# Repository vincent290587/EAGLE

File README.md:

# EAGLE

Here is a list of Eagle library files, useful if you want to use SD cards, Dynastream ANT+ chips, Freescale MCUs or a STC3100 to monitor current consumption and battery discharge level.

- N548: Dynastream N548/N550/N5150 M8 footprint module
- ANTAP28: Dynastream N548/N550/N5150 M4 footprint module
- D52Q: Dynastream new D52Q module, using nRF52832 from Nordic
- nRF52840: Nordic bluetooth 5 new chip
- MK20DN512: Footprint for Freescale 100 pins MKxx family (MK20, MK64.......)

- FlashMem: Footprint for SPI flash chips like Microchip SST25VF & SS26VF

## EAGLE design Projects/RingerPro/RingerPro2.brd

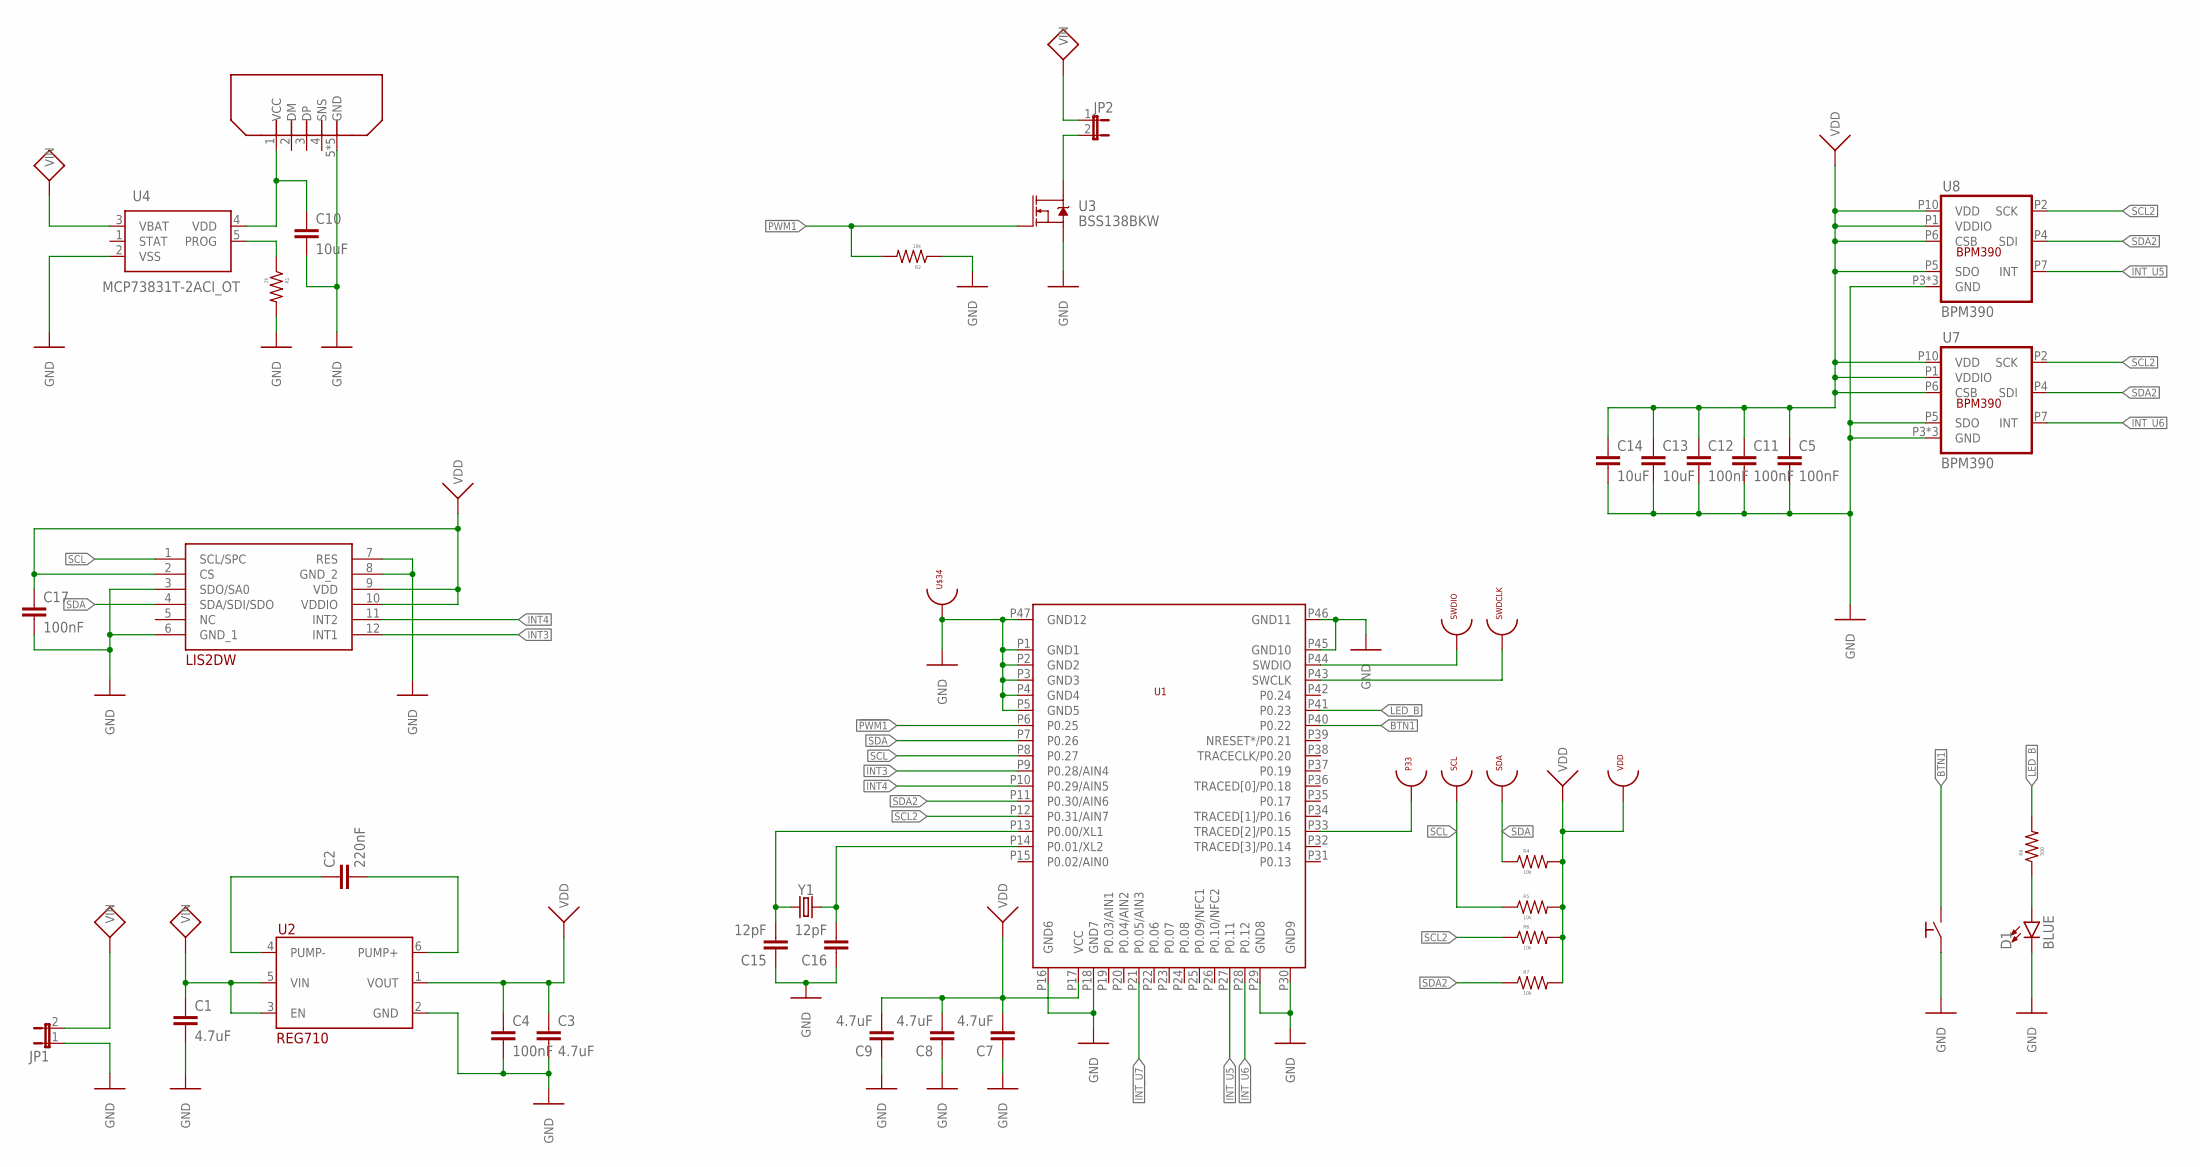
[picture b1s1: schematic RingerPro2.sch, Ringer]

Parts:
C1, C3, C7, C8, C9: 4.7uF; C0603
C2: 220nF; C0603
C4, C5, C11, C12, C17: 100nF; C0603
C10, C13, C14: 10uF; C0603
C15, C16: 12pF; C0603
D1: BLUE; LED-0603
IC1: LIS2DW12TR; LGA-12
JP1, JP2: JP1E; JP1
P33: TESTPOINT_22
R1: 2k; R0603
R2, R4, R5, R6, R7: 10k; R0603
R9: 500; R0603
SCL: TESTPOINT_22
SDA: TESTPOINT_22
SPST1: PTS526SK08; PTS526SKG15SMTR2LFS
SWDCLK: TESTPOINT_22
SWDIO: TESTPOINT_22
U1: BMD-300
U2: REG710; SOT457
U3: BSS138BKW; SOT65P210X110-3N
U4: MCP73831T-2ACI_OT; SOT95P270X145-5N
U7, U8: BPM390
U$23: ZX80B5P
U$34: TESTPOINT_22
VDD: TESTPOINT_22
Y1: CRYSTALSMD-3.2X1.5; CRYSTAL-SMD-3.2X1.5MM

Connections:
!PWM1: R2.2, U1.P6 (P0.25), U3.1 (G)
BTN1: SPST1.3, SPST1.4, U1.P40 (P0.22)
GND: C1.2, C3.2, C4.2, C5.2, C7.1, C8.1, C9.1, C10.2, C11.2, C12.2, C13.2, C14.2, C15.1, C16.1, C17.2, D1.C, IC1.3 (SDO/SA0), IC1.6 (GND_1), IC1.7 (RES), IC1.8 (GND_2), JP1.1, R1.2, R2.1, SPST1.1, SPST1.2, U1.P1 (GND1), U1.P2 (GND2), U1.P3 (GND3), U1.P4 (GND4), U1.P5 (GND5), U1.P16 (GND6), U1.P18 (GND7), U1.P29 (GND8), U1.P30 (GND9), U1.P45 (GND10), U1.P46 (GND11), U1.P47 (GND12), U2.2 (GND), U3.2 (S), U4.2 (VSS), U7.P3 (GND), U7.P5 (SDO), U7.P8 (GND), U7.P9 (GND), U8.P3 (GND), U8.P8 (GND), U8.P9 (GND), U$23.5 (GND), U$23.GND1 (GND), U$23.GND2 (GND), U$23.GND3 (GND), U$23.GND4 (GND), U$34.P$1
INT3: IC1.12 (INT1), U1.P9 (P0.28/AIN4)
INT4: IC1.11 (INT2), U1.P10 (P0.29/AIN5)
INT_U5: U1.P27 (P0.11), U8.P7 (INT)
INT_U6: U1.P28 (P0.12), U7.P7 (INT)
INT_U7: U1.P21 (P0.05/AIN3)
LED_B: R9.2, U1.P41 (P0.23)
unnamed: C2.1, U2.4 (PUMP-)
unnamed: C2.2, U2.6 (PUMP+)
unnamed: C10.1, U4.4 (VDD), U$23.1 (VCC)
unnamed: C15.2, U1.P13 (P0.00/XL1), Y1.P$1 (1)
unnamed: R1.1, U4.5 (PROG)
unnamed: JP2.2, U3.3 (D)
unnamed: C16.2, U1.P14 (P0.01/XL2), Y1.P$2 (2)
unnamed: P33.P$1, U1.P33 (TRACED[2]/P0.15)
unnamed: D1.A, R9.1
SCL: IC1.1 (SCL/SPC), R5.1, SCL.P$1, U1.P8 (P0.27)
SCL2: R6.1, U1.P12 (P0.31/AIN7), U7.P2 (SCK), U8.P2 (SCK)
SDA: IC1.4 (SDA/SDI/SDO), R4.1, SDA.P$1, U1.P7 (P0.26)
SDA2: R7.1, U1.P11 (P0.30/AIN6), U7.P4 (SDI), U8.P4 (SDI)
SWCLK: SWDCLK.P$1, U1.P43 (SWCLK)
SWDIO: SWDIO.P$1, U1.P44 (SWDIO)
VDD: C3.1, C4.1, C5.1, C7.2, C8.2, C9.2, C11.1, C12.1, C13.1, C14.1, C17.1, IC1.2 (CS), IC1.9 (VDD), IC1.10 (VDDIO), R4.2, R5.2, R6.2, R7.2, U1.P17 (VCC), U2.1 (VOUT), U7.P1 (VDDIO), U7.P6 (CSB), U7.P10 (VDD), U8.P1 (VDDIO), U8.P5 (SDO), U8.P6 (CSB), U8.P10 (VDD), VDD.P$1
VIN: C1.1, JP1.2, JP2.1, U2.3 (EN), U2.5 (VIN), U4.3 (VBAT)

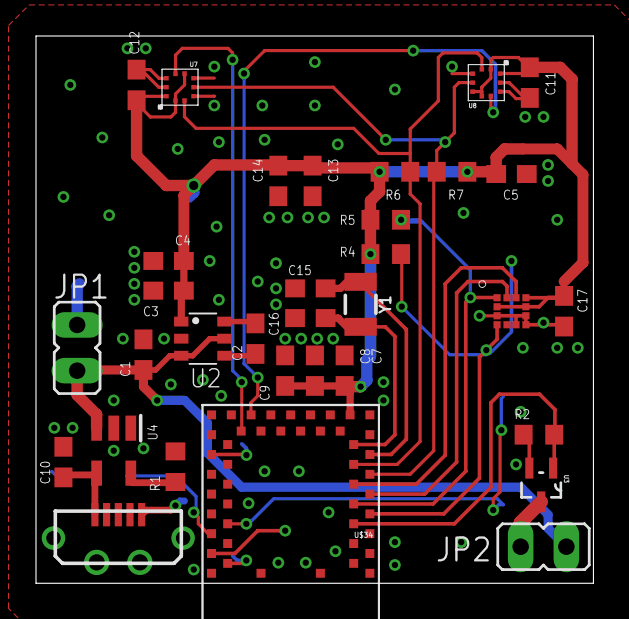
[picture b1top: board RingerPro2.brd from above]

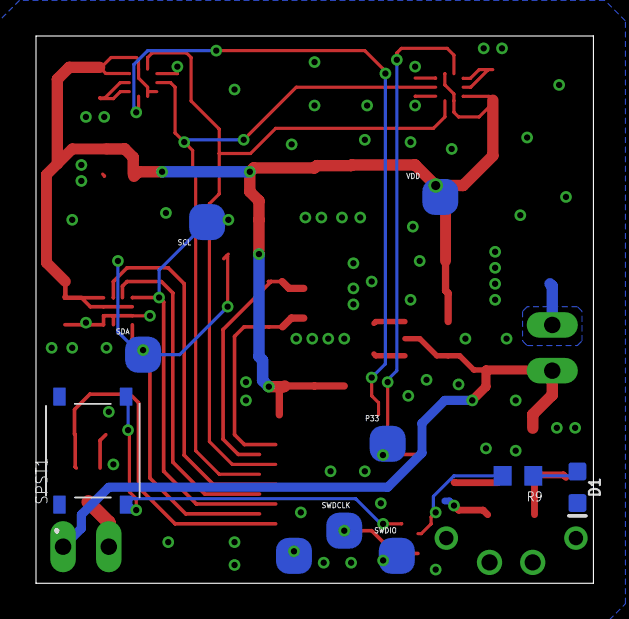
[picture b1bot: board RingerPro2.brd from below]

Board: 2 copper layers, 31.0 x 30.4 mm, 43 parts (10 on the bottom side), 25 nets.

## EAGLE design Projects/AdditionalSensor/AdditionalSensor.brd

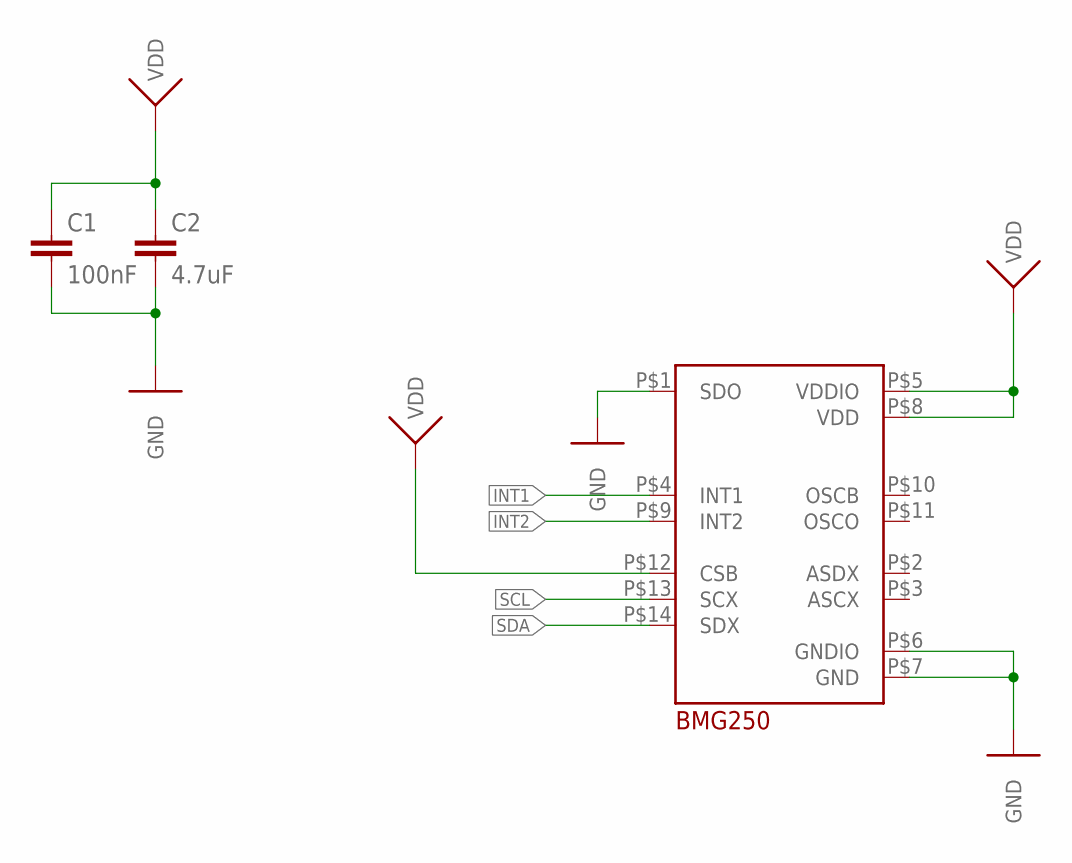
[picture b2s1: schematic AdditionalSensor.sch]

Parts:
C1: 100nF; C0603
C2: 4.7uF; C0603
U1: BMG250; LGA14

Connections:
GND: C1.2, C2.2, U1.P$1 (SDO), U1.P$6 (GNDIO), U1.P$7 (GND)
INT1: U1.P$4 (INT1)
INT2: U1.P$9 (INT2)
SCL: U1.P$13 (SCX)
SDA: U1.P$14 (SDX)
VDD: C1.1, C2.1, U1.P$5 (VDDIO), U1.P$8 (VDD), U1.P$12 (CSB)

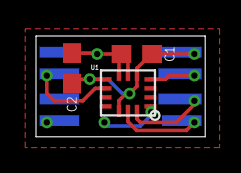
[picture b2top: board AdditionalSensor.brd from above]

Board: 2 copper layers, 9.4 x 5.6 mm, 3 parts (0 on the bottom side), 2 nets.

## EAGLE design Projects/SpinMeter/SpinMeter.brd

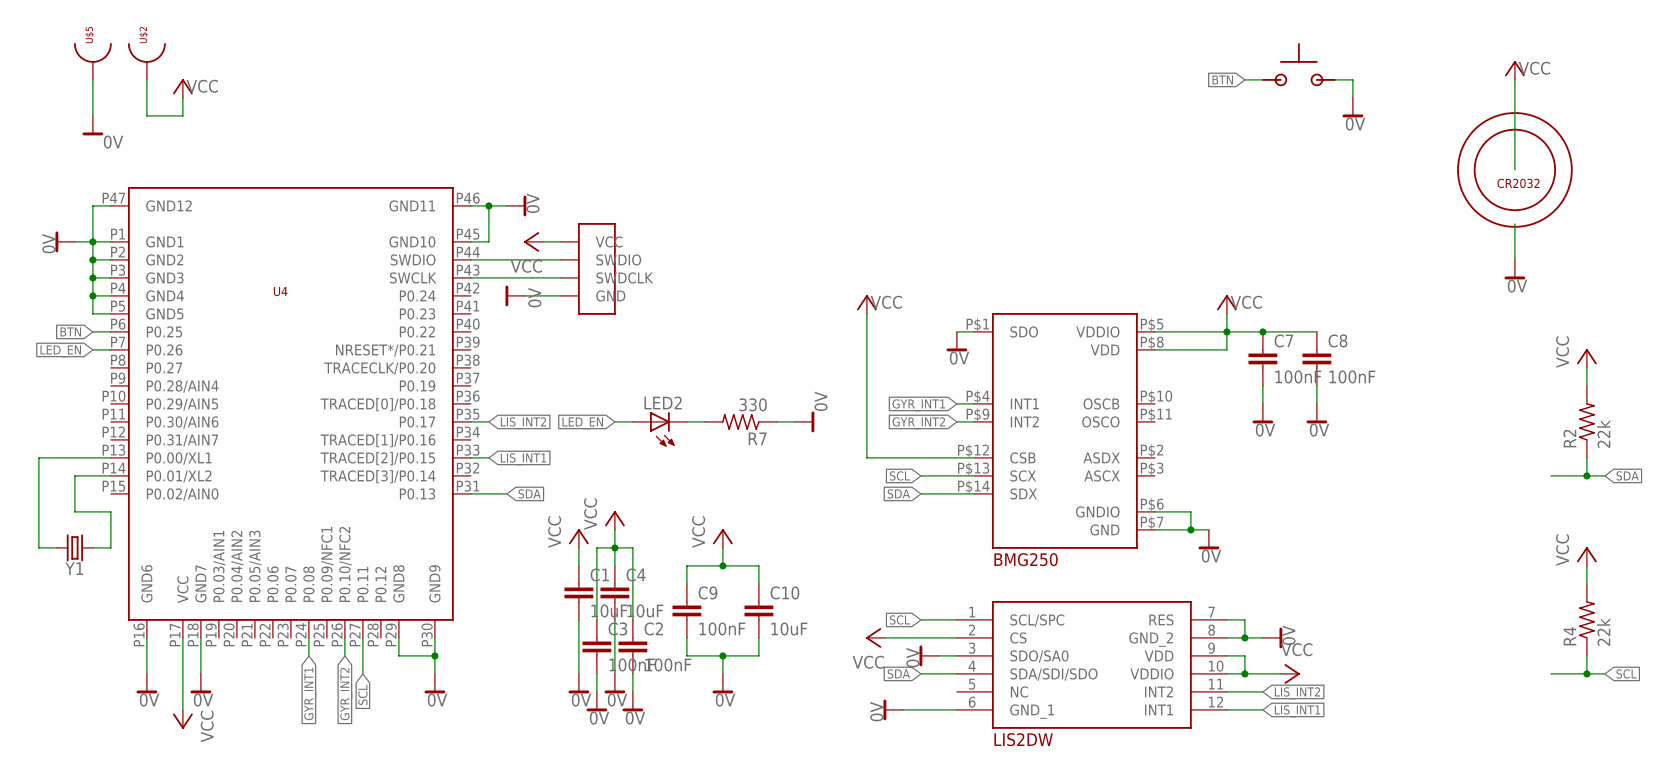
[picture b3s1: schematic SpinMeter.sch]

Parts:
C1, C4, C10: 10uF; C0603
C2, C3, C7, C8, C9: 100nF; C0603
IC1: LIS2DW12TR; LGA-12
LED2: LEDCHIP-LED0603; CHIP-LED0603
R2, R4: 22k; R0603
R7: 330; R0603
U1: BMG250; LGA14
U3: BAT-HLD-001-THM; BATHLD001THM
U4: BMD-300
U$1: PROG_SMD
U$2, U$5: TESTPOINT_22
U$10: SKRMAAE010
Y1: CRYSTALSMD-3.2X1.5; CRYSTAL-SMD-3.2X1.5MM

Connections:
0V: C1.2, C2.2, C3.2, C4.2, C7.2, C8.2, C9.2, C10.2, IC1.3 (SDO/SA0), IC1.6 (GND_1), IC1.7 (RES), IC1.8 (GND_2), R7.1, U1.P$1 (SDO), U1.P$6 (GNDIO), U1.P$7 (GND), U3.5 (-), U4.P1 (GND1), U4.P2 (GND2), U4.P3 (GND3), U4.P4 (GND4), U4.P5 (GND5), U4.P16 (GND6), U4.P18 (GND7), U4.P29 (GND8), U4.P30 (GND9), U4.P45 (GND10), U4.P46 (GND11), U4.P47 (GND12), U$1.GND, U$5.P$1, U$10.P$2, U$10.P$4
BTN: U4.P6 (P0.25), U$10.P$1, U$10.P$3
GYR_INT1: U1.P$4 (INT1), U4.P24 (P0.08)
GYR_INT2: U1.P$9 (INT2), U4.P26 (P0.10/NFC2)
LED_EN: LED2.A, U4.P7 (P0.26)
LIS_INT1: IC1.12 (INT1), U4.P33 (TRACED[2]/P0.15)
LIS_INT2: IC1.11 (INT2), U4.P35 (P0.17)
unnamed: U4.P44 (SWDIO), U$1.PIN2 (SWDIO)
unnamed: U4.P43 (SWCLK), U$1.PIN1 (SWDCLK)
unnamed: LED2.C, R7.2
unnamed: U4.P13 (P0.00/XL1), Y1.P$2 (2)
unnamed: U4.P14 (P0.01/XL2), Y1.P$1 (1)
SCL: IC1.1 (SCL/SPC), R4.1, U1.P$13 (SCX), U4.P27 (P0.11)
SDA: IC1.4 (SDA/SDI/SDO), R2.1, U1.P$14 (SDX), U4.P31 (P0.13)
VCC: C1.1, C2.1, C3.1, C4.1, C7.1, C8.1, C9.1, C10.1, IC1.2 (CS), IC1.9 (VDD), IC1.10 (VDDIO), R2.2, R4.2, U1.P$5 (VDDIO), U1.P$8 (VDD), U1.P$12 (CSB), U3.1 (+), U3.2 (+), U3.3 (+), U3.4 (+), U4.P17 (VCC), U$1.VCC, U$2.P$1

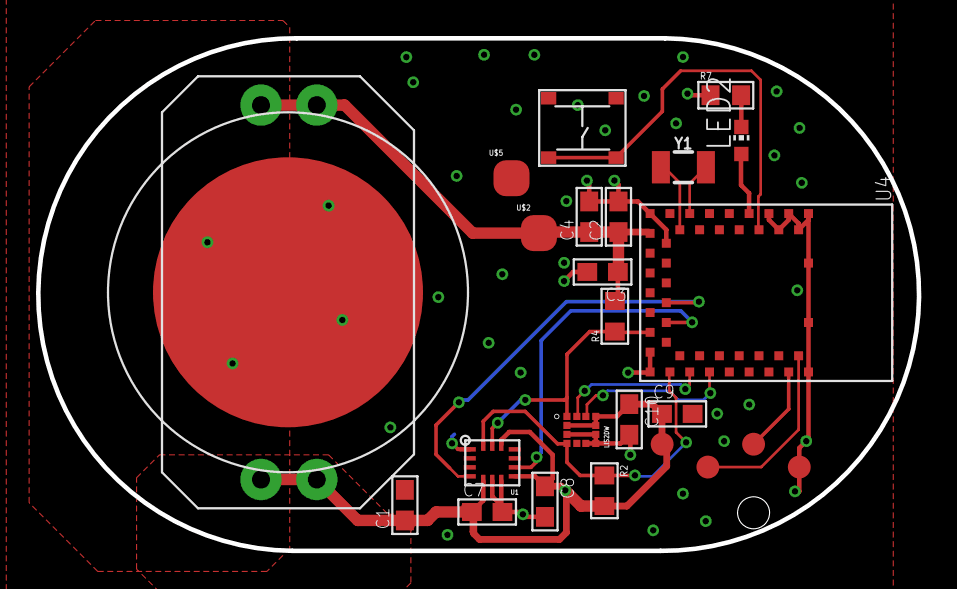
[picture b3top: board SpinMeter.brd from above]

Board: 2 copper layers, 48.9 x 28.5 mm, 21 parts (0 on the bottom side), 15 nets.

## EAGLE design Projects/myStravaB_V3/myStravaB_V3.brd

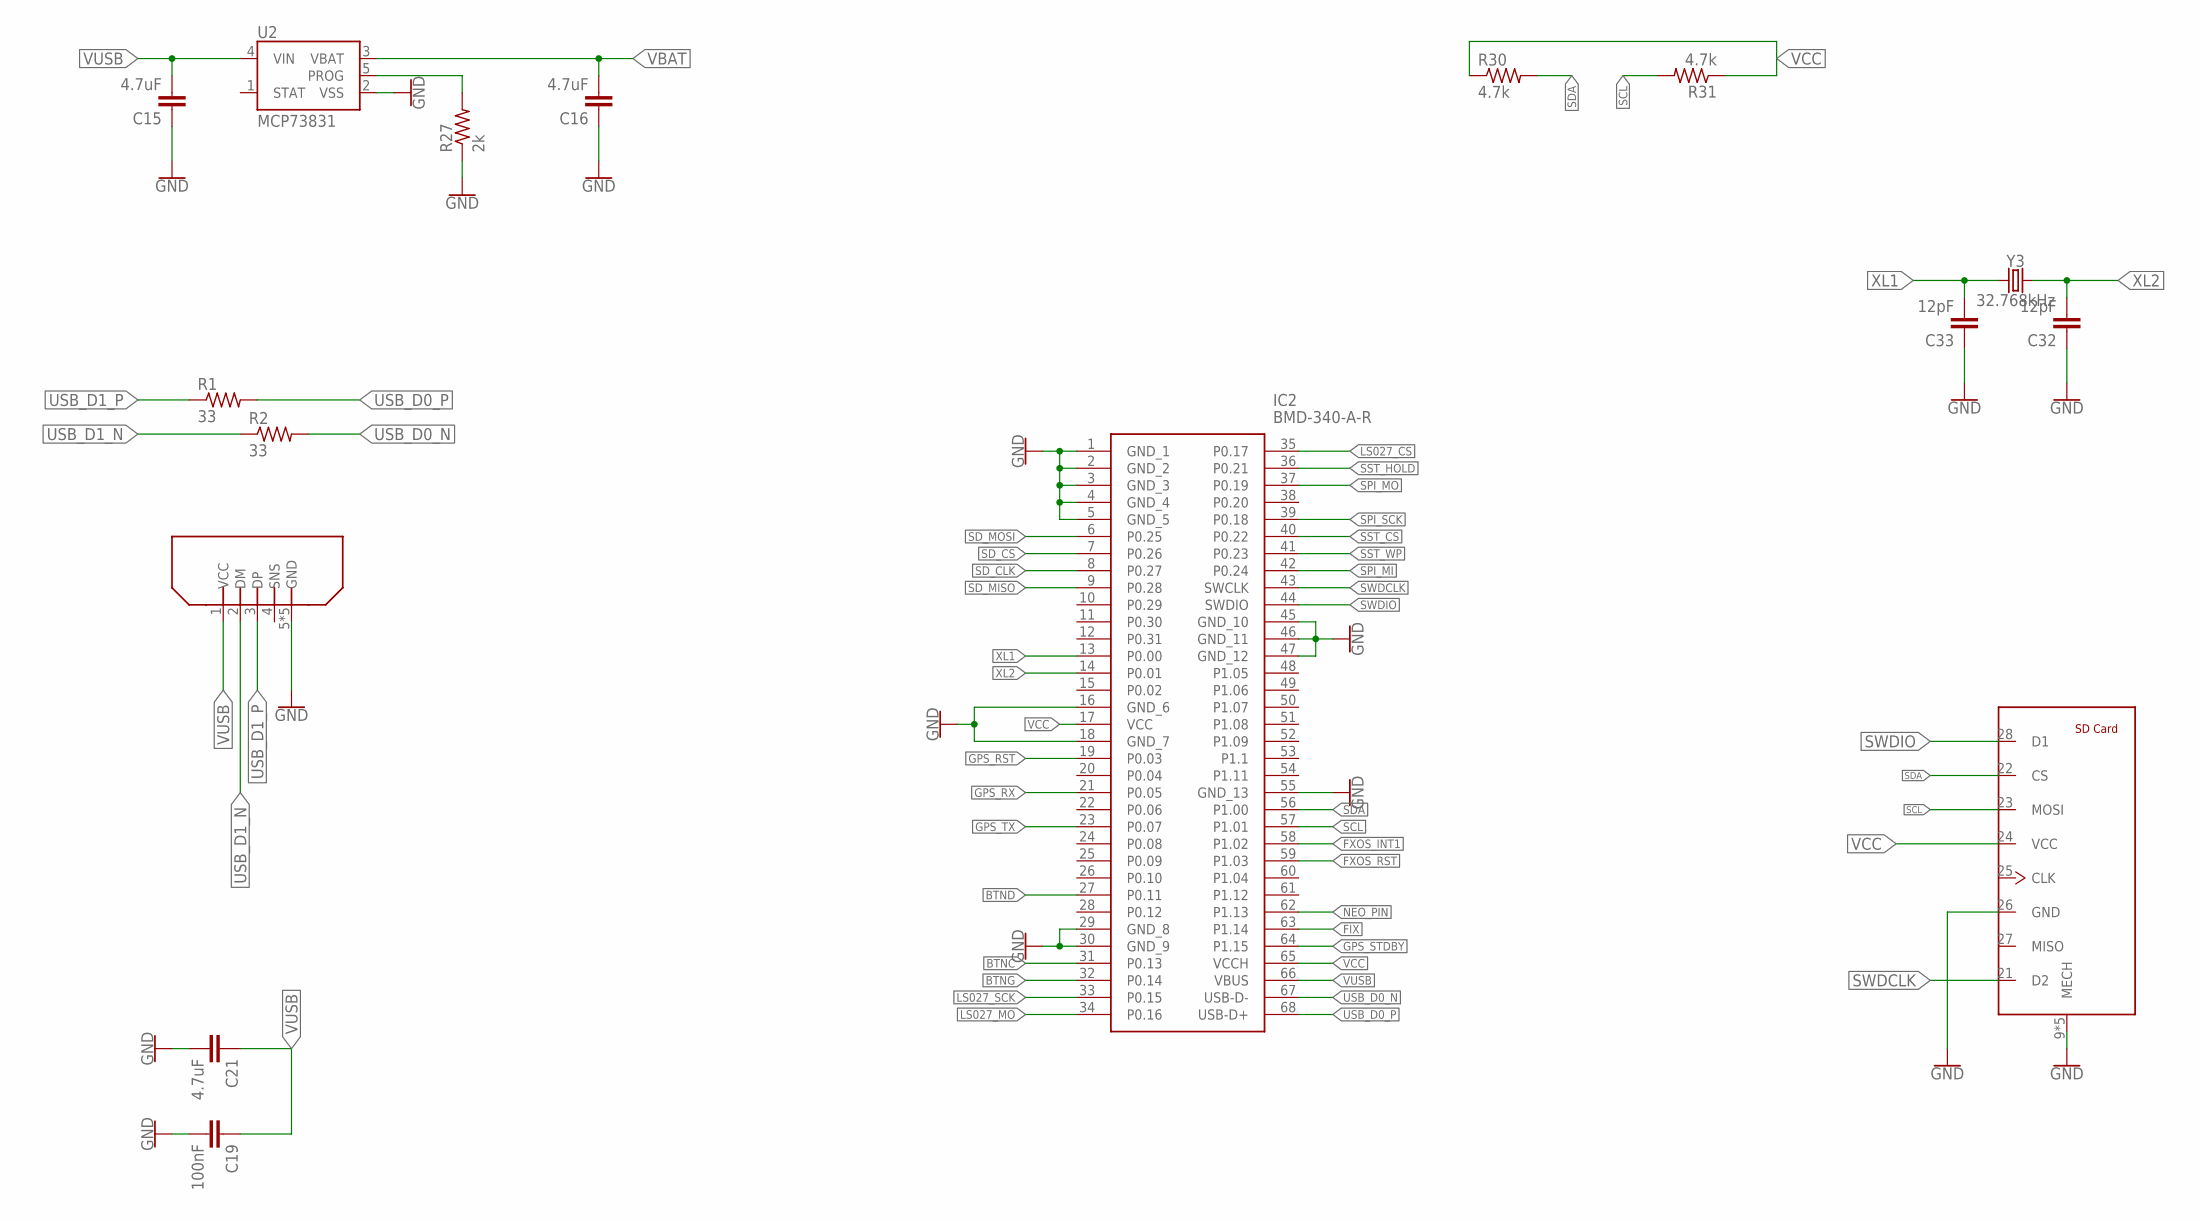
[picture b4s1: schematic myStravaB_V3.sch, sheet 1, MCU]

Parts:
C15, C16, C21: 4.7uF; C0805
C19: 100nF; C0603
C32, C33: 12pF; C0603
IC2: BMD-340-A-R; BMD340AR
J1: 47571-0001
R1, R2: 33; R0603
R27: 2k; R0603
R30, R31: 4.7k; R0603
U2: MCP73831; SOT23-5
U$3: ZX80B5P
Y3: 32.768kHz; CRYSTAL-SMD-3.2X1.5MM

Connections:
BTNC: IC2.31 (P0.13); also elsewhere on the board
BTND: IC2.27 (P0.11); also elsewhere on the board
BTNG: IC2.32 (P0.14); also elsewhere on the board
FIX: IC2.63 (P1.14); also elsewhere on the board
FXOS_INT1: IC2.58 (P1.02); also elsewhere on the board
FXOS_RST: IC2.59 (P1.03); also elsewhere on the board
GND: C15.1, C16.1, C19.2, C21.2, C32.1, C33.1, IC2.1 (GND_1), IC2.2 (GND_2), IC2.3 (GND_3), IC2.4 (GND_4), IC2.5 (GND_5), IC2.16 (GND_6), IC2.18 (GND_7), IC2.29 (GND_8), IC2.30 (GND_9), IC2.45 (GND_10), IC2.46 (GND_11), IC2.47 (GND_12), IC2.55 (GND_13), J1.9 (MECH), J1.10 (MECH), J1.11 (MECH), J1.12 (MECH), J1.13 (MECH), J1.26 (GND), R27.1, U2.2 (VSS), U$3.5 (GND), U$3.GND1 (GND), U$3.GND2 (GND), U$3.GND3 (GND), U$3.GND4 (GND); also elsewhere on the board
GPS_RST: IC2.19 (P0.03); also elsewhere on the board
GPS_RX: IC2.21 (P0.05); also elsewhere on the board
GPS_STDBY: IC2.64 (P1.15); also elsewhere on the board
GPS_TX: IC2.23 (P0.07); also elsewhere on the board
LS027_CS: IC2.35 (P0.17); also elsewhere on the board
LS027_MO: IC2.34 (P0.16); also elsewhere on the board
LS027_SCK: IC2.33 (P0.15); also elsewhere on the board
unnamed: R27.2, U2.5 (PROG)
NEO_PIN: IC2.62 (P1.13); also elsewhere on the board
SCL: IC2.57 (P1.01), J1.23 (MOSI), R31.2; also elsewhere on the board
SDA: IC2.56 (P1.00), J1.22 (CS), R30.2; also elsewhere on the board
SD_CLK: IC2.8 (P0.27); also elsewhere on the board
SD_CS: IC2.7 (P0.26); also elsewhere on the board
SD_MISO: IC2.9 (P0.28); also elsewhere on the board
SD_MOSI: IC2.6 (P0.25); also elsewhere on the board
SPI_MI: IC2.42 (P0.24); also elsewhere on the board
SPI_MO: IC2.37 (P0.19); also elsewhere on the board
SPI_SCK: IC2.39 (P0.18); also elsewhere on the board
SST_CS: IC2.40 (P0.22); also elsewhere on the board
SST_HOLD: IC2.36 (P0.21); also elsewhere on the board
SST_WP: IC2.41 (P0.23); also elsewhere on the board
SWDCLK: IC2.43 (SWCLK), J1.21 (D2)
SWDIO: IC2.44 (SWDIO), J1.28 (D1)
USB_D0_N: IC2.67 (USB-D-), R2.2
USB_D0_P: IC2.68 (USB-D+), R1.2
USB_D1_N: R2.1, U$3.2 (DM)
USB_D1_P: R1.1, U$3.3 (DP)
VBAT: C16.2, U2.3 (VBAT); also elsewhere on the board
VCC: IC2.17 (VCC), IC2.65 (VCCH), J1.24 (VCC), R30.1, R31.1; also elsewhere on the board
VUSB: C15.2, C19.1, C21.1, IC2.66 (VBUS), U2.4 (VIN), U$3.1 (VCC); also elsewhere on the board
XL1: C33.2, IC2.13 (P0.00), Y3.P$1 (1)
XL2: C32.2, IC2.14 (P0.01), Y3.P$2 (2)

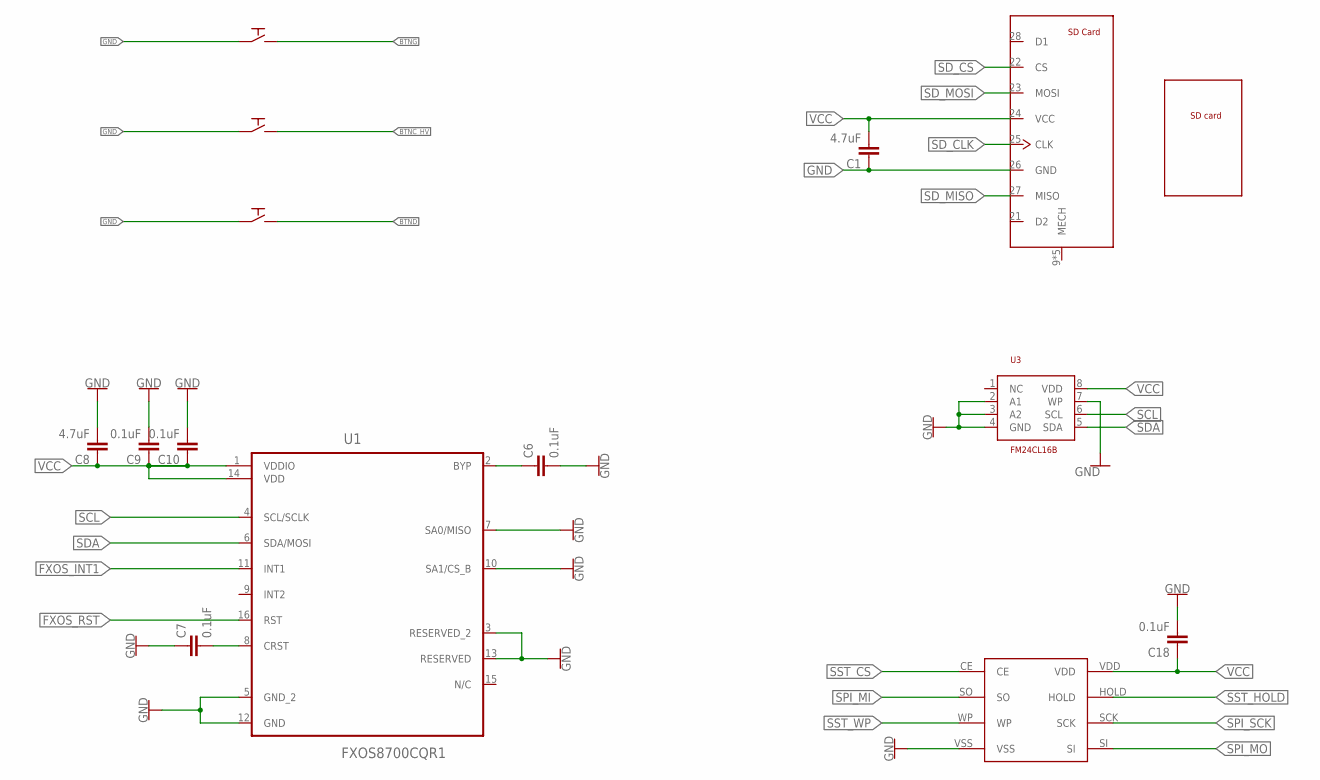
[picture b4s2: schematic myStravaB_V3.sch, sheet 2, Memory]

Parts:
B1: MICRO-SD_FOOTPRINT; MICRO-SD-FOOTPRINT
C1, C8: 4.7uF; 0603
C6, C7, C9, C10, C18: 0.1uF; 0603
SD: 47571-0001
SPST1, SPST2, SPST3: PTS526SK08; PTS526SKG15SMTR2LFS
U1: FXOS8700CQR1; QFN50P300X300X120-16N
U3: FM24CL16B; SOIC127P600X175-8N
U$2: FLASH; SOIC8

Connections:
BTNC_HV: SPST2.3, SPST2.4; also elsewhere on the board
BTND: SPST3.3, SPST3.4; also elsewhere on the board
BTNG: SPST1.3, SPST1.4; also elsewhere on the board
BYP: C6.1, U1.2 (BYP)
CRST: C7.2, U1.8 (CRST)
FXOS_INT1: U1.11 (INT1); also elsewhere on the board
FXOS_RST: U1.16 (RST); also elsewhere on the board
GND: C1.1, C6.2, C7.1, C8.2, C9.2, C10.2, C18.2, SD.26 (GND), SPST1.1, SPST1.2, SPST2.1, SPST2.2, SPST3.1, SPST3.2, U1.3 (RESERVED_2), U1.5 (GND_2), U1.7 (SA0/MISO), U1.10 (SA1/CS_B), U1.12 (GND), U1.13 (RESERVED), U3.2 (A1), U3.3 (A2), U3.4 (GND), U3.7 (WP), U$2.VSS; also elsewhere on the board
SCL: U1.4 (SCL/SCLK), U3.6 (SCL); also elsewhere on the board
SDA: U1.6 (SDA/MOSI), U3.5 (SDA); also elsewhere on the board
SD_CLK: SD.25 (CLK); also elsewhere on the board
SD_CS: SD.22 (CS); also elsewhere on the board
SD_MISO: SD.27 (MISO); also elsewhere on the board
SD_MOSI: SD.23 (MOSI); also elsewhere on the board
SPI_MI: U$2.SO; also elsewhere on the board
SPI_MO: U$2.SI; also elsewhere on the board
SPI_SCK: U$2.SCK; also elsewhere on the board
SST_CS: U$2.CE; also elsewhere on the board
SST_HOLD: U$2.HOLD; also elsewhere on the board
SST_WP: U$2.WP; also elsewhere on the board
VCC: C1.2, C8.1, C9.1, C10.1, C18.1, SD.24 (VCC), U1.1 (VDDIO), U1.14 (VDD), U3.8 (VDD), U$2.VDD; also elsewhere on the board

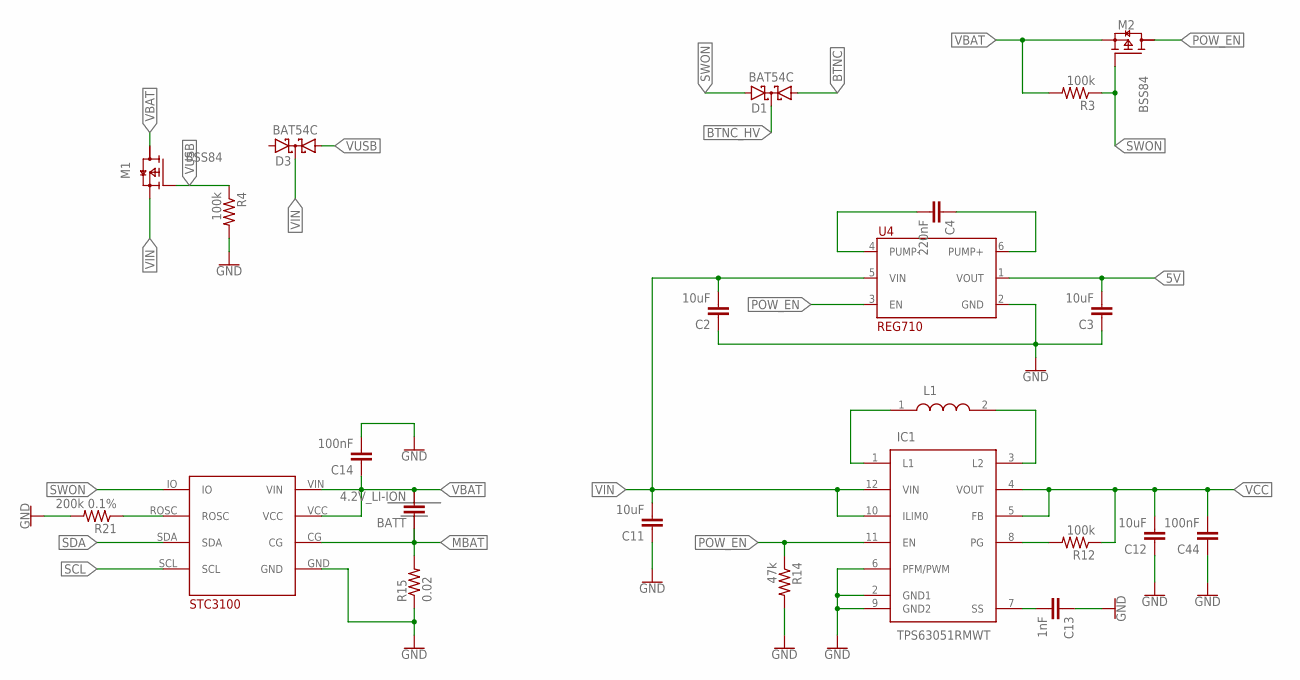
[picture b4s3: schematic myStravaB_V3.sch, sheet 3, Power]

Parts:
BATT: 4.2V_LI-ION; C1210
C2, C3, C11: 10uF; C0805
C4: 220nF; C0805
C12: 10uF; C0603
C13: 1nF; C0603
C14, C44: 100nF; C0603
D1, D3: BAT54C; SOT23
IC1: TPS63051RMWT; QFN50P250X250X100-12N
L1: 1269AS-H-1R5M=P2; INDC2520X110N
M1, M2: BSS84; SOT65P210X110-3N
R3, R4, R12: 100k; R0603
R14: 47k; R0603
R15: 0.02; R0603
R21: 200k 0.1%; R0603
U4: REG710; SOT457
U$6: STC3100

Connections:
5V: C3.2, U4.1 (VOUT); also elsewhere on the board
BTNC: D1.1 (A1); also elsewhere on the board
BTNC_HV: D1.3 (CC); also elsewhere on the board
GND: C2.1, C3.1, C11.1, C12.1, C13.1, C14.2, C44.1, IC1.2 (GND1), IC1.6 (PFM/PWM), IC1.9 (GND2), R4.2, R14.2, R15.1, R21.2, U4.2 (GND), U$6.GND; also elsewhere on the board
L1: IC1.1 (L1), L1.1
L2: IC1.3 (L2), L1.2
MBAT: BATT.1, R15.2, U$6.CG
unnamed: C4.1, U4.6 (PUMP+)
unnamed: C4.2, U4.4 (PUMP-)
PG: IC1.8 (PG), R12.2
POW_EN: IC1.11 (EN), M2.3 (D), R14.1, U4.3 (EN)
ROSC: R21.1, U$6.ROSC
SCL: U$6.SCL; also elsewhere on the board
SDA: U$6.SDA; also elsewhere on the board
SS: C13.2, IC1.7 (SS)
SWON: D1.2 (A2), M2.1 (G), R3.1, U$6.IO
VBAT: BATT.2, C14.1, M1.3 (D), M2.2 (S), R3.2, U$6.VCC, U$6.VIN; also elsewhere on the board
VCC: C12.2, C44.2, IC1.4 (VOUT), IC1.5 (FB), R12.1; also elsewhere on the board
VIN: C2.2, C11.2, D3.3 (CC), IC1.10 (ILIM0), IC1.12 (VIN), M1.2 (S), U4.5 (VIN)
VUSB: D3.1 (A1), M1.1 (G), R4.1; also elsewhere on the board

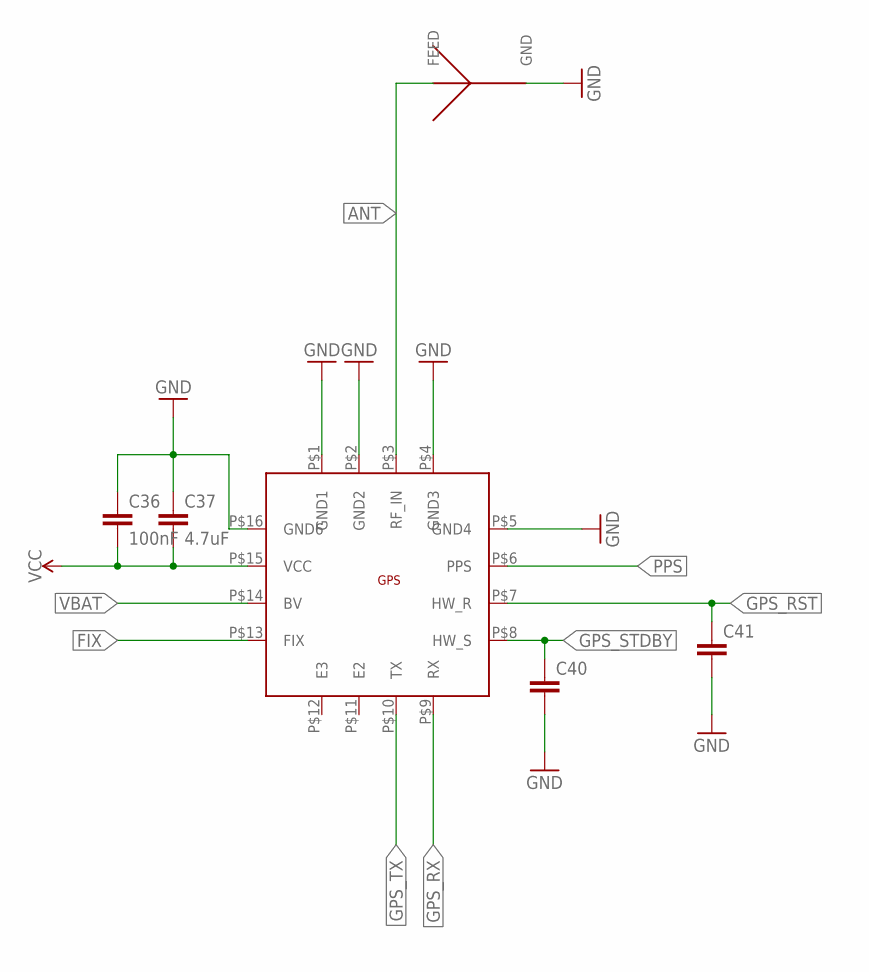
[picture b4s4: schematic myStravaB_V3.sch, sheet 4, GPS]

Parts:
C36: 100nF; C0603
C37: 4.7uF; C0603
C40, C41: C-EUC0603; C0603
U$4: SR4G008
U$5: M10578-A3; M10578

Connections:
ANT: U$4.P$2 (FEED), U$5.P$3 (RF_IN)
FIX: U$5.P$13 (FIX); also elsewhere on the board
GND: C36.1, C37.1, C40.2, C41.2, U$4.P$3 (GND), U$4.P$4 (GND), U$4.P$6 (GND), U$5.P$1 (GND1), U$5.P$2 (GND2), U$5.P$4 (GND3), U$5.P$5 (GND4), U$5.P$16 (GND6); also elsewhere on the board
GPS_RST: C41.1, U$5.P$7 (HW_R); also elsewhere on the board
GPS_RX: U$5.P$9 (RX); also elsewhere on the board
GPS_STDBY: C40.1, U$5.P$8 (HW_S); also elsewhere on the board
GPS_TX: U$5.P$10 (TX); also elsewhere on the board
PPS: U$5.P$6 (PPS)
VBAT: U$5.P$14 (BV); also elsewhere on the board
VCC: C36.2, C37.2, U$5.P$15 (VCC); also elsewhere on the board

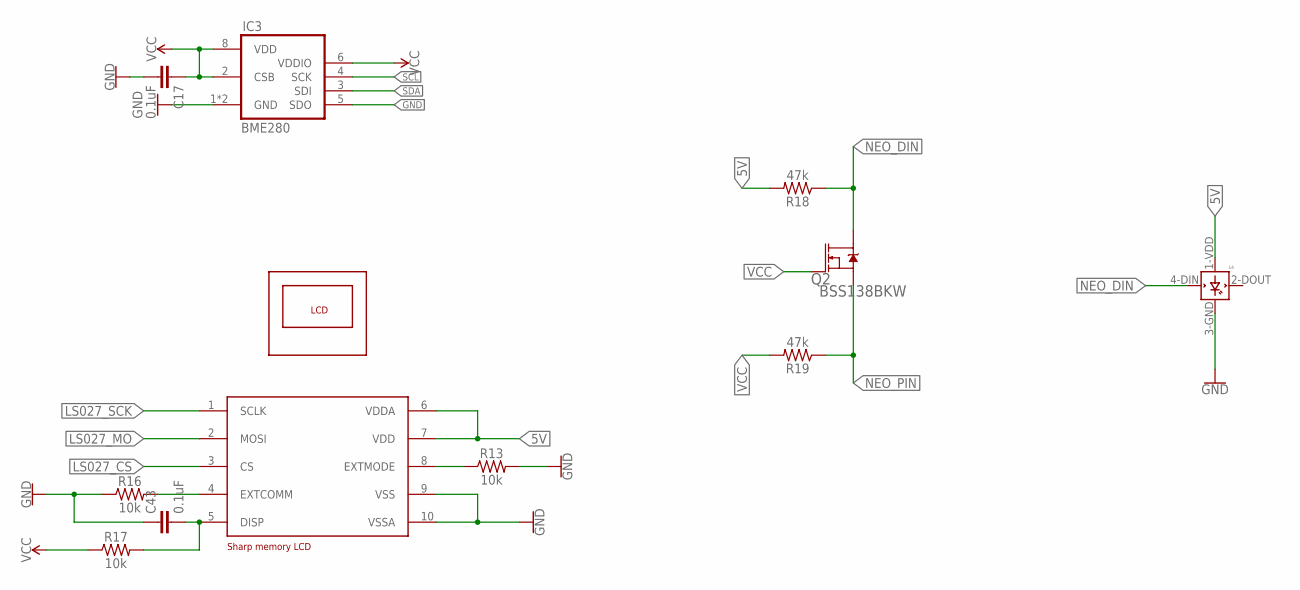
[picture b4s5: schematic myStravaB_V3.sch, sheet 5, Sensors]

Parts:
C17, C43: 0.1uF; 0603
IC3: BME280
L4: WS2812B
Q2: BSS138BKW; SOT65P210X110-3N
R13, R16, R17: 10k; 0603
R18, R19: 47k; 0603
U$15: SHARP27_FOOTPRINT; LCD27
U$16: SHARP27

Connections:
5V: L4.1-VDD (VDD), R18.2, U$16.6 (VDDA), U$16.7 (VDD); also elsewhere on the board
DISP1: C43.2, R17.2, U$16.5 (DISP)
EXTCOMM1: R16.2, U$16.4 (EXTCOMM)
EXTMODE1: R13.1, U$16.8 (EXTMODE)
GND: C17.2, C43.1, IC3.1 (GND), IC3.5 (SDO), IC3.7 (GND), L4.3-GND (GND), R13.2, R16.1, U$16.9 (VSS), U$16.10 (VSSA); also elsewhere on the board
LS027_CS: U$16.3 (CS); also elsewhere on the board
LS027_MO: U$16.2 (MOSI); also elsewhere on the board
LS027_SCK: U$16.1 (SCLK); also elsewhere on the board
NEO_DIN: L4.4-DIN (DIN), Q2.3 (D), R18.1
NEO_PIN: Q2.2 (S), R19.1; also elsewhere on the board
SCL: IC3.4 (SCK); also elsewhere on the board
SDA: IC3.3 (SDI); also elsewhere on the board
VCC: C17.1, IC3.2 (CSB), IC3.6 (VDDIO), IC3.8 (VDD), Q2.1 (G), R17.1, R19.2; also elsewhere on the board

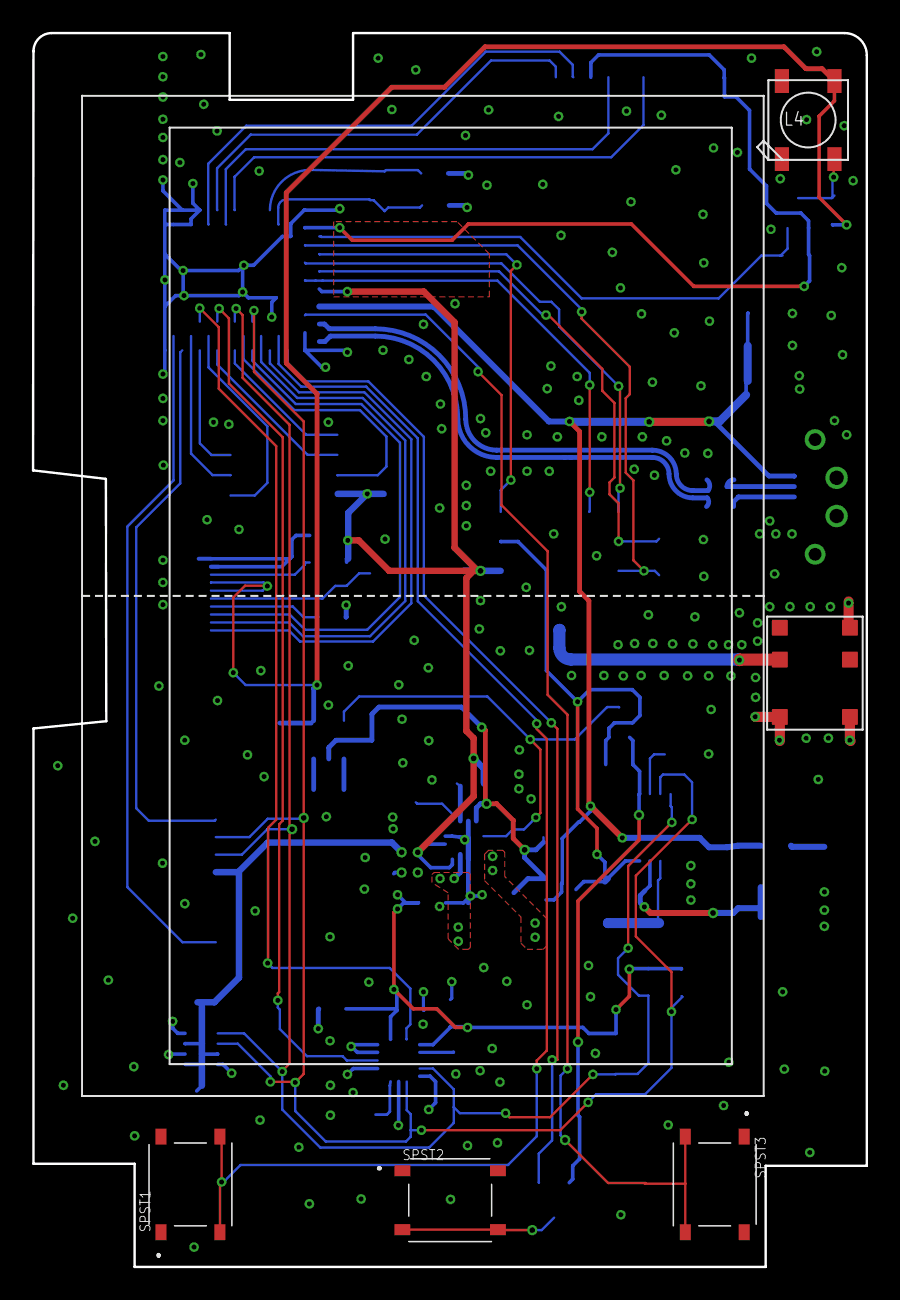
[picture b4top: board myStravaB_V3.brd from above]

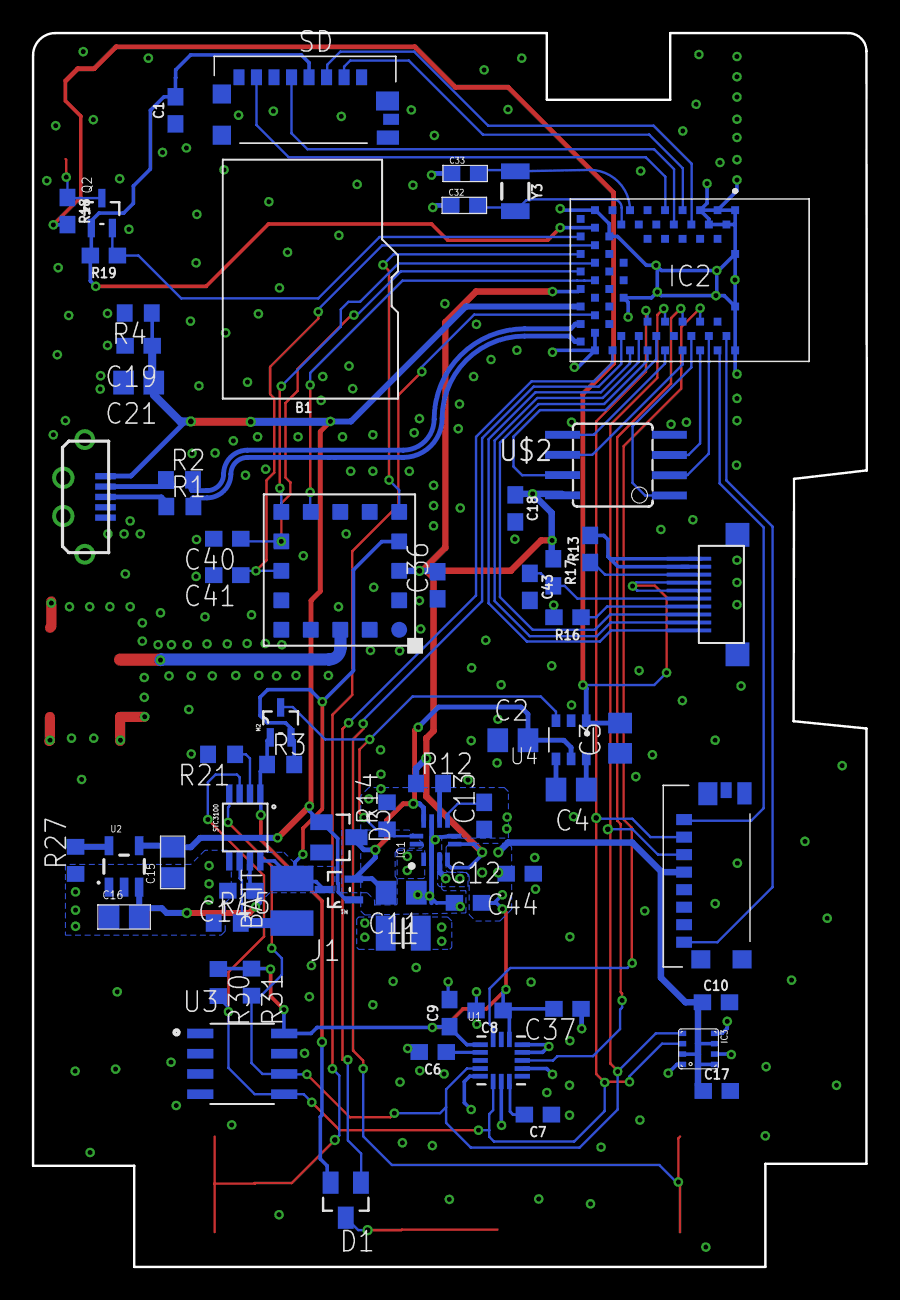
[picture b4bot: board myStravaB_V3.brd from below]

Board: 2 copper layers, 52.3 x 77.5 mm, 72 parts (65 on the bottom side), 59 nets.

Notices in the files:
parts and their libraries:
SparkFun-Resistors: Licensing: Creative Commons ShareAlike 4.0 International - https://creativecommons.org/licenses/by-sa/4.0
